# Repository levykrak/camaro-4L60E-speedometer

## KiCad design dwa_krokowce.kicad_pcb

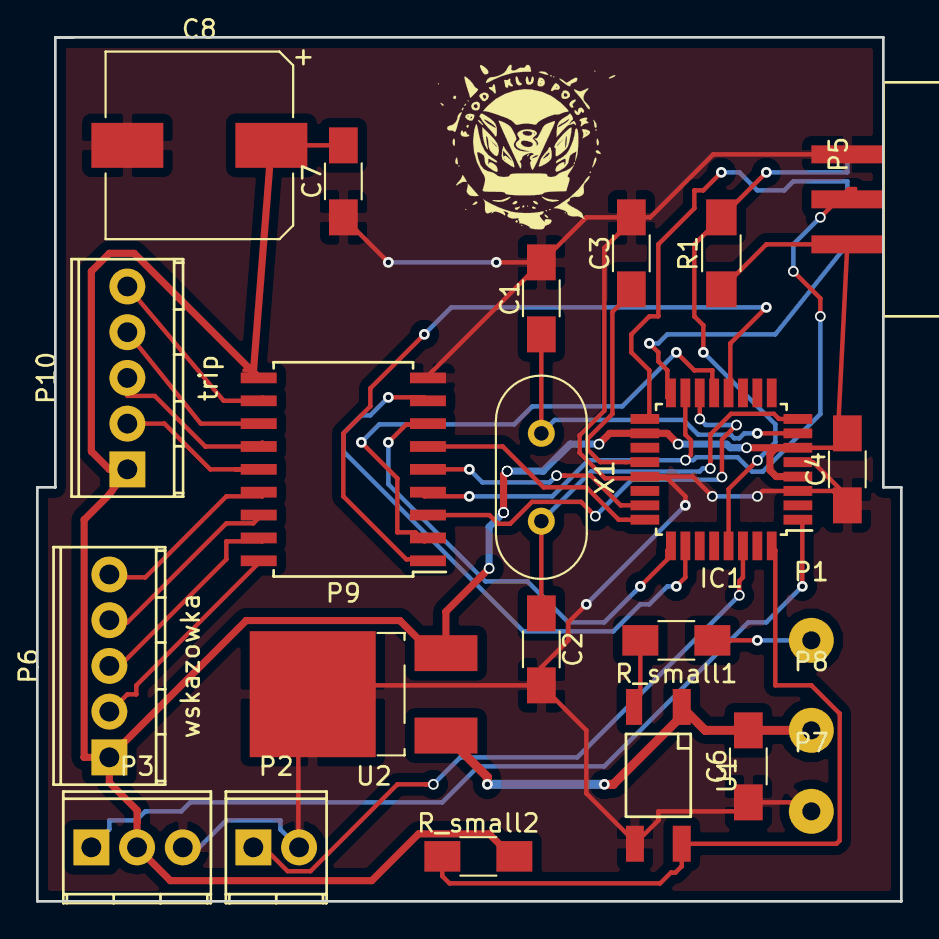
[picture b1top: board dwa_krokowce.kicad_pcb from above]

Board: 2 copper layers, 48.0 x 48.0 mm, 23 parts (0 on the bottom side), 30 nets.

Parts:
C1, C2: 27pF; C_1206_HandSoldering
C3, C4, C6, C7: 100nF; C_1206_HandSoldering
C8: 100uF; CP_Elec_10x10
IC1: ATMEGA8-MI-serwo; TQFP-32_7x7mm_Pitch0.8mm
P1: VSS; SolderWirePad_single_1mmDrill
P2: switch; TerminalBlock_Pheonix_MPT-2.54mm_2pol
P3: PA3; TerminalBlock_Pheonix_MPT-2.54mm_3pol
P5: CONN_3X2; ISP-6
P6: wskazowka; TerminalBlock_Pheonix_MPT-2.54mm_5pol
P7: GND; SolderWirePad_single_1mmDrill
P8: +12V; SolderWirePad_single_1mmDrill
P9: ULN2803A wysterowanie; SOIC-18W_7.5x11.6mm_Pitch1.27mm
P10: trip; TerminalBlock_Pheonix_MPT-2.54mm_5pol
R1: 10k; R_1206_HandSoldering
R_small1: 620; R_1206_HandSoldering
R_small2: 1k; R_1206_HandSoldering
U1: LTV-814; Optocoupler_SMD_HandSoldering_LTV-814
U2: LM7805; TO-252-2Lead
X1: 16MHz; Crystal_HC49-U_Vertical

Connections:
+5V: C4.2, C7.2, C8.1, IC1.4, IC1.6, IC1.18, P3.2, P5.2, P6.1, P9.10, P10.1, R1.1, R_small2.2, U2.VO
+12V: C6.2, P8.1, U1.1, U2.VI
/VSS_impuls: IC1.32, R_small2.1, U1.4
/trip1: IC1.23, P9.5
/trip2: IC1.24, P9.6
/trip3: IC1.25, P9.7
/trip4: IC1.26, P9.8
/wskaz1: IC1.12, P9.1
/wskaz2: IC1.13, P9.2
/wskaz3: IC1.14, P9.3
GND: C1.2, C2.2, C3.2, C4.1, C6.1, C7.1, C8.2, IC1.3, IC1.5, IC1.21, P2.2, P3.3, P5.6, P7.1, P9.9, U1.3, U2.GND
MISO: IC1.16, P5.1
MOSI: IC1.15, P5.4, P9.4
unnamed: C1.1, IC1.7, X1.1
unnamed: C2.1, IC1.8, X1.2
unnamed: C3.1, IC1.20
unnamed: IC1.1, P3.1
unnamed: IC1.30, P2.1
unnamed: P1.1, R_small1.1
unnamed: P6.2, P9.18
unnamed: P6.3, P9.17
unnamed: P6.4, P9.16
unnamed: P6.5, P9.15
unnamed: P9.14, P10.2
unnamed: P9.13, P10.3
unnamed: P9.12, P10.4
unnamed: P9.11, P10.5
unnamed: R_small1.2, U1.2
RST: IC1.29, P5.5, R1.2
SCK: IC1.17, P5.3

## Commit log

2018-10-20 v 1.0 - working need to adjust some things
2020-01-09 excel sheet with freqency
2020-01-09 gauge photos added
